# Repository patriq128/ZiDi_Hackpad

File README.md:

# ZiDi_Hackpad

My Hackpad is a 6-key macropad with an OLED display, rotary encoder, and my own custom firmware.

## Features

* 6 keys in a matrix
* EC11 rotary encoder
* 128x32 OLED display
* Custom firmware

## CAD Model

I am not very experienced with CAD, but I gave it a try.

The case is held together with 4 M3 bolts and heat-set inserts. The PCB is not directly mounted to the case; instead, it is supported by external supports that keep it securely in position.

The case consists of two parts: a bottom and a top. I left a small gap between the parts to make sure they fit together properly.

Made in **Onshape**.

## PCB

The PCB was designed in **KiCad**.

### Schematic

The schematic is quite basic, but it works.

### PCB

## Firmware

I decided to make the firmware a separate project, so you can find it here:

The `Firmware` folder contains everything you need to run the firmware, including a `conf.json` file with some example modes.

The `production` folder contains `firmware.uf2`, which is the CircuitPython firmware compiled and packaged as a UF2 file, ready to be flashed onto the device.

> Want to create something similar yourself? Check out this guide: [Create Custom UF2 File for Easy CircuitPython Flashing](https://embeddedcomputing.com/technology/open-source/create-custom-uf2-file-for-easy-circuitpython-flashing)

## BOM

* 6x Cherry MX switches
* 6x DSA keycaps
* 6x 1N4148 DO-35 diodes
* 1x 0.91" 128x32 OLED display
* 1x EC11 rotary encoder
* 1x XIAO RP2040
* 4x M3x16mm screws
* 4x M3x5mm heat-set inserts
* 1x 3D-printed case

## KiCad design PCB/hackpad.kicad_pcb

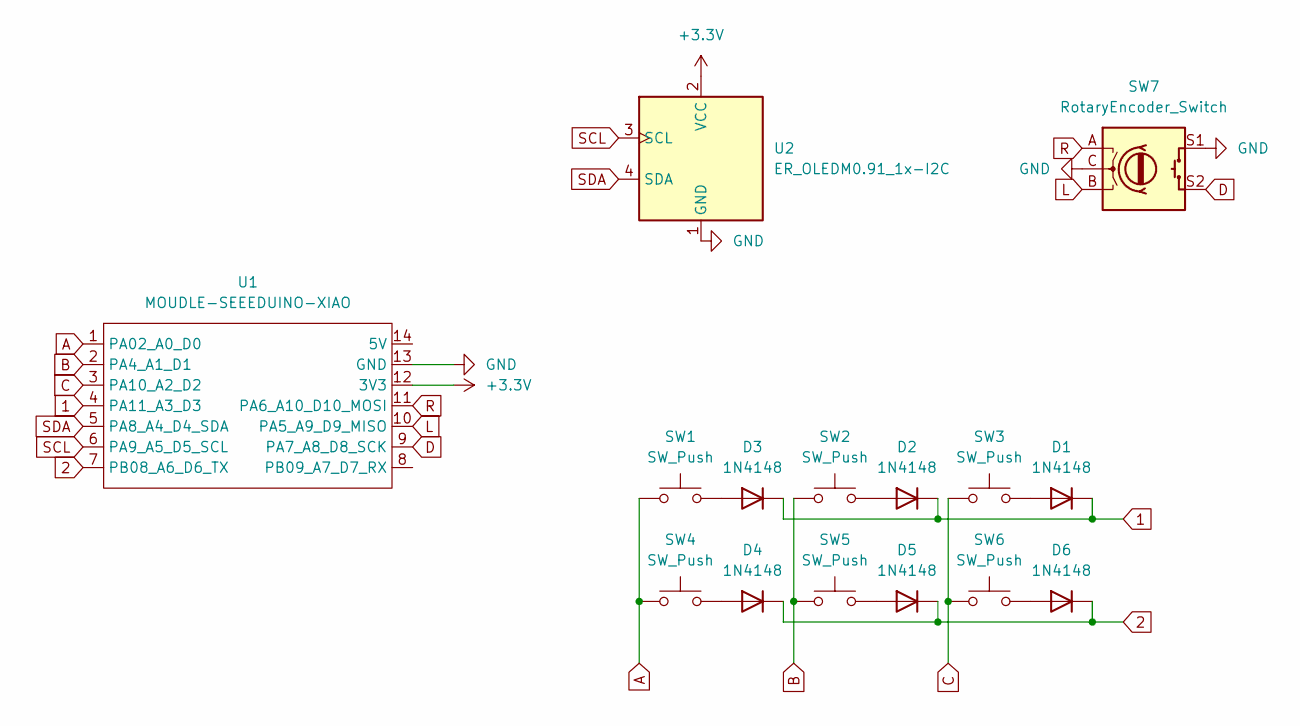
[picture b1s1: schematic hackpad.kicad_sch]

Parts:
D1, D2, D3, D4, D5, D6: 1N4148; D_DO-35_SOD27_P7.62mm_Horizontal
SW1, SW2, SW3, SW4, SW5, SW6: SW_Push; SW_Cherry_MX_1.00u_PCB
SW7: RotaryEncoder_Switch; RotaryEncoder_Alps_EC11E-Switch_Vertical_H20mm
U1: MOUDLE-SEEEDUINO-XIAO; XIAO-Generic-Hybrid-14P-2.54-21X17.8MM
U2: ER_OLEDM0.91_1x-I2C

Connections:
1: D1.1 (K), D2.1 (K), D3.1 (K), U1.4 (PA11_A3_D3)
2: D4.1 (K), D5.1 (K), D6.1 (K), U1.7 (PB08_A6_D6_TX)
+3.3V: U1.12 (3V3), U2.2 (VCC)
A: SW1.1, SW4.1, U1.1 (PA02_A0_D0)
B: SW2.1, SW5.1, U1.2 (PA4_A1_D1)
C: SW3.1, SW6.1, U1.3 (PA10_A2_D2)
D: SW7.S2, U1.9 (PA7_A8_D8_SCK)
GND: SW7.C, SW7.S1, U1.13 (GND), U2.1 (GND)
L: SW7.B, U1.10 (PA5_A9_D9_MISO)
unnamed: D1.2 (A), SW3.2
unnamed: D2.2 (A), SW2.2
unnamed: D3.2 (A), SW1.2
unnamed: D4.2 (A), SW4.2
unnamed: D5.2 (A), SW5.2
unnamed: D6.2 (A), SW6.2
R: SW7.A, U1.11 (PA6_A10_D10_MOSI)
SCL: U1.6 (PA9_A5_D5_SCL), U2.3 (SCL)
SDA: U1.5 (PA8_A4_D4_SDA), U2.4 (SDA)

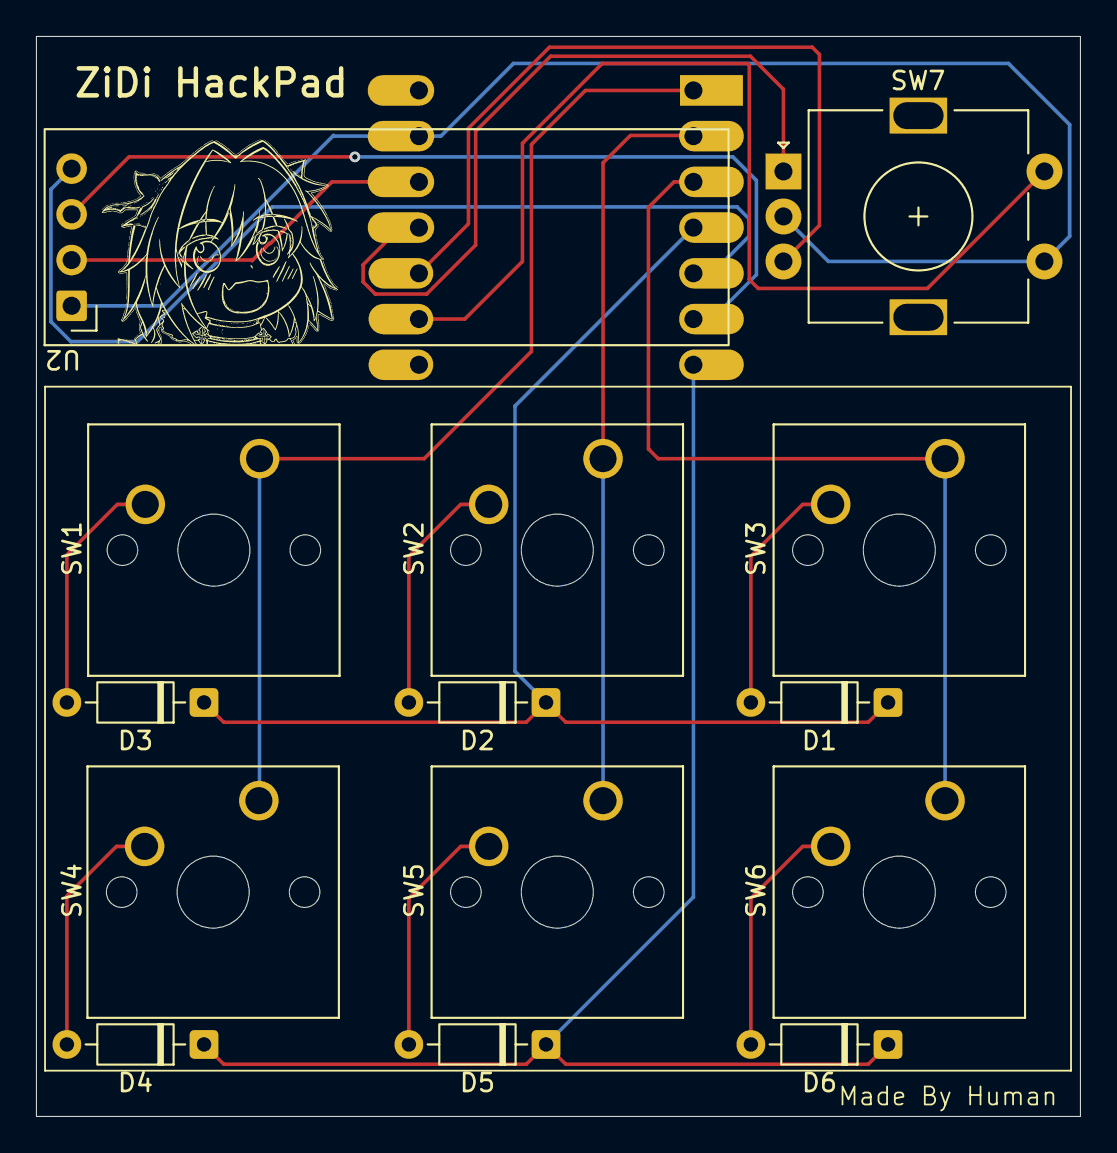
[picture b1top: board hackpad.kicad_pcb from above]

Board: 2 copper layers, 58.0 x 60.0 mm, 15 parts (1 on the bottom side), 18 nets.
